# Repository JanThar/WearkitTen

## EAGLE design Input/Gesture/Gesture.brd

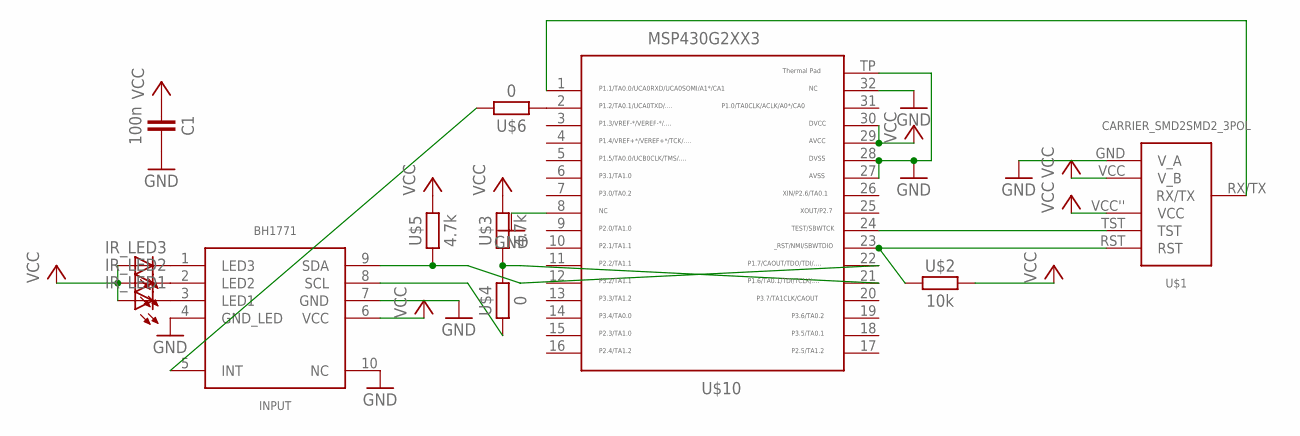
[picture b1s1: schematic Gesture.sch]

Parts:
C1: 100n; 603
INPUT: BH1771
IR_LED1, IR_LED2, IR_LED3: LEDCHIP-LED0603; CHIP-LED0603
U$1: CARRIER_SMD2SMD2_3POL; CARRIER_SMD2_3POL
U$2: 10k; 603
U$3, U$5: 4.7k; 603
U$4, U$6: 0; 603
U$10: MSP430G2553; QFN32

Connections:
GND: C1.2, INPUT.4 (GND_LED), INPUT.7 (GND), INPUT.10 (NC), U$1.GND (V_A), U$10.8, U$10.27, U$10.28, U$10.32, U$10.TP
unnamed: U$6.1, U$10.2
unnamed: U$1.TST, U$10.24
unnamed: U$1.RST, U$2.1, U$10.23
unnamed: U$3.1, U$4.2, U$10.21
unnamed: INPUT.5 (INT), U$6.2
unnamed: U$1.RX/TX, U$10.1
unnamed: INPUT.9 (SDA), U$5.1, U$10.22
unnamed: INPUT.8 (SCL), U$4.1
unnamed: INPUT.1 (LED3), IR_LED3.C
unnamed: INPUT.2 (LED2), IR_LED2.C
unnamed: INPUT.3 (LED1), IR_LED1.C
VCC: C1.1, INPUT.6 (VCC), IR_LED1.A, IR_LED2.A, IR_LED3.A, U$1.VCC (V_B), U$1.VCC'' (VCC), U$2.2, U$3.2, U$5.2, U$10.29, U$10.30

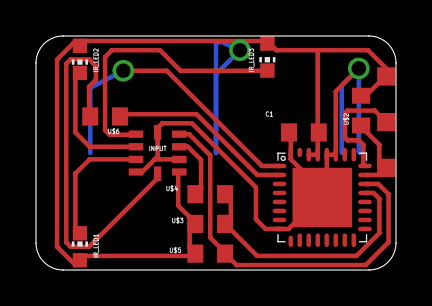
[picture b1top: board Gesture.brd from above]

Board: 2 copper layers, 20.0 x 13.0 mm, 12 parts (0 on the bottom side), 13 nets.

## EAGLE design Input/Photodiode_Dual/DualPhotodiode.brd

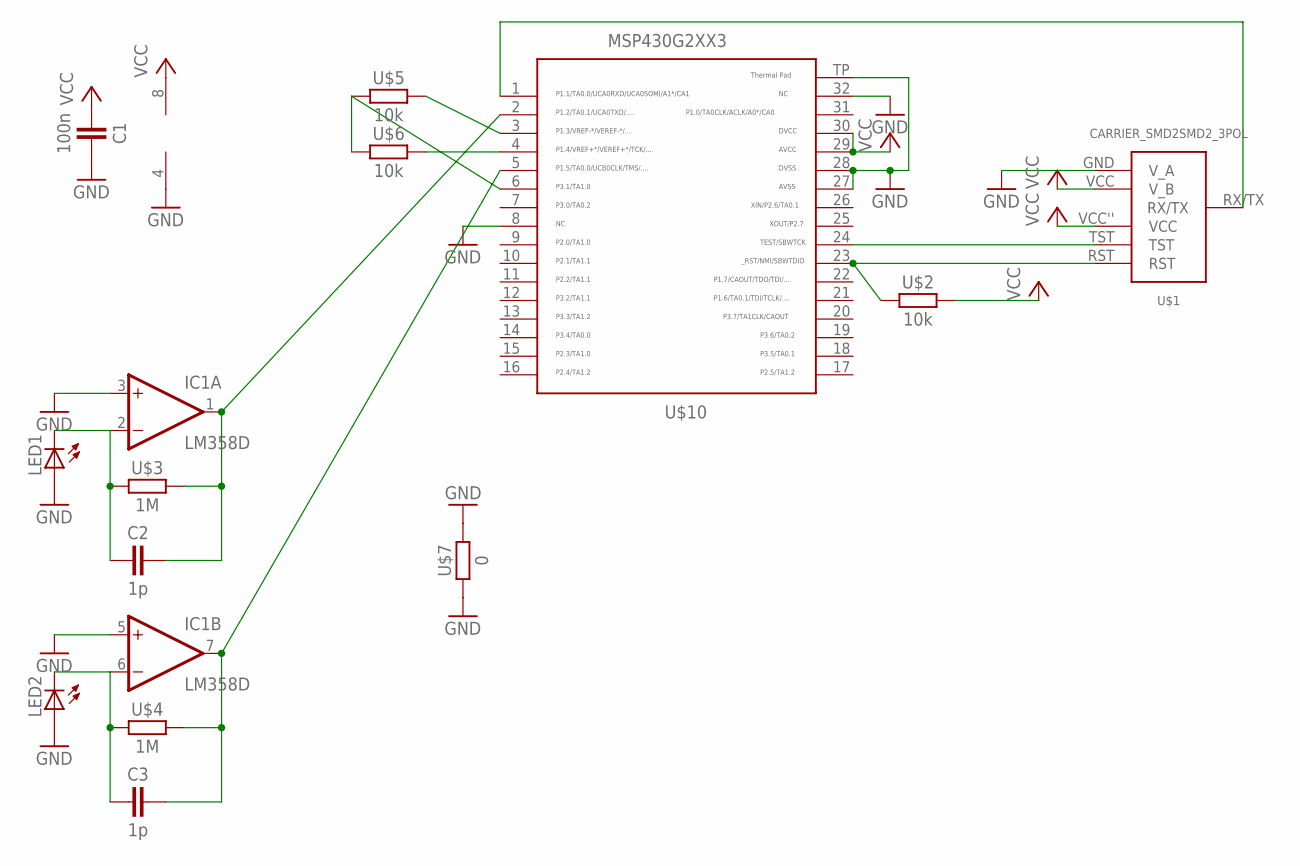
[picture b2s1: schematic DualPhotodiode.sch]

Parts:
C1: 100n; 603
C2, C3: 1p; 603
IC1: LM358D; SO08
LED1, LED2: LEDCHIP-LED0805; CHIP-LED0805
U$1: CARRIER_SMD2SMD2_3POL; CARRIER_SMD2_3POL
U$2, U$5, U$6: 10k; 603
U$3, U$4: 1M; 603
U$7: 0; 603
U$10: MSP430G2553; QFN32

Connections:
GND: C1.2, IC1.3 (+IN), IC1.4 (V-), IC1.5 (+IN), LED1.A, LED2.A, U$1.GND (V_A), U$7.1, U$7.2, U$10.8, U$10.27, U$10.28, U$10.32, U$10.TP
unnamed: C2.1, IC1.2 (-IN), LED1.C, U$3.1
unnamed: U$1.TST, U$10.24
unnamed: U$1.RST, U$2.1, U$10.23
unnamed: U$5.2, U$10.3
unnamed: C3.1, IC1.6 (-IN), LED2.C, U$4.1
unnamed: C3.2, IC1.7 (OUT), U$4.2, U$10.5
unnamed: C2.2, IC1.1 (OUT), U$3.2, U$10.2
unnamed: U$1.RX/TX, U$10.1
unnamed: U$6.2, U$10.4
unnamed: U$5.1, U$6.1, U$10.6
VCC: C1.1, IC1.8 (V+), U$1.VCC (V_B), U$1.VCC'' (VCC), U$2.2, U$10.29, U$10.30

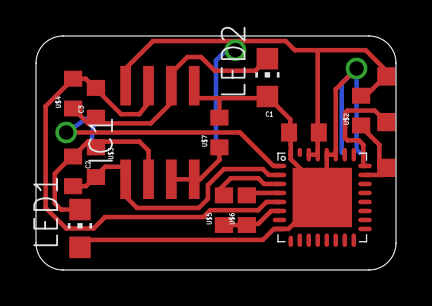
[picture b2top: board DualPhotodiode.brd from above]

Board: 2 copper layers, 20.0 x 13.0 mm, 14 parts (0 on the bottom side), 12 nets.

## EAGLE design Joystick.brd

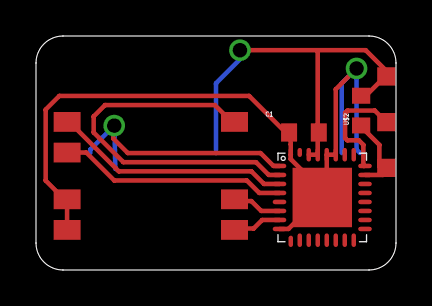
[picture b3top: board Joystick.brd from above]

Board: 2 copper layers, 20.0 x 13.0 mm, 5 parts (0 on the bottom side), 10 nets.

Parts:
C1: 100n; 603
U$1: CARRIER_SMD2SMD2_3POL; CARRIER_SMD2_3POL
U$2: 10k; 603
U$3: JOYSTICK
U$10: MSP430G2553; QFN32

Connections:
D: U$3.D4, U$10.7
GND: C1.2, U$1.GND, U$3.C1, U$3.C2, U$10.8, U$10.27, U$10.28, U$10.32, U$10.TP
L: U$3.L7, U$10.3
unnamed: U$1.TST, U$10.24
unnamed: U$1.RST, U$2.1, U$10.23
unnamed: U$1.RX/TX, U$10.1
R: U$3.R6, U$10.4
SELECT: U$3.S5, U$10.2
U: U$3.U3, U$10.6
VCC: C1.1, U$1.VCC, U$1.VCC'', U$2.2, U$10.29, U$10.30

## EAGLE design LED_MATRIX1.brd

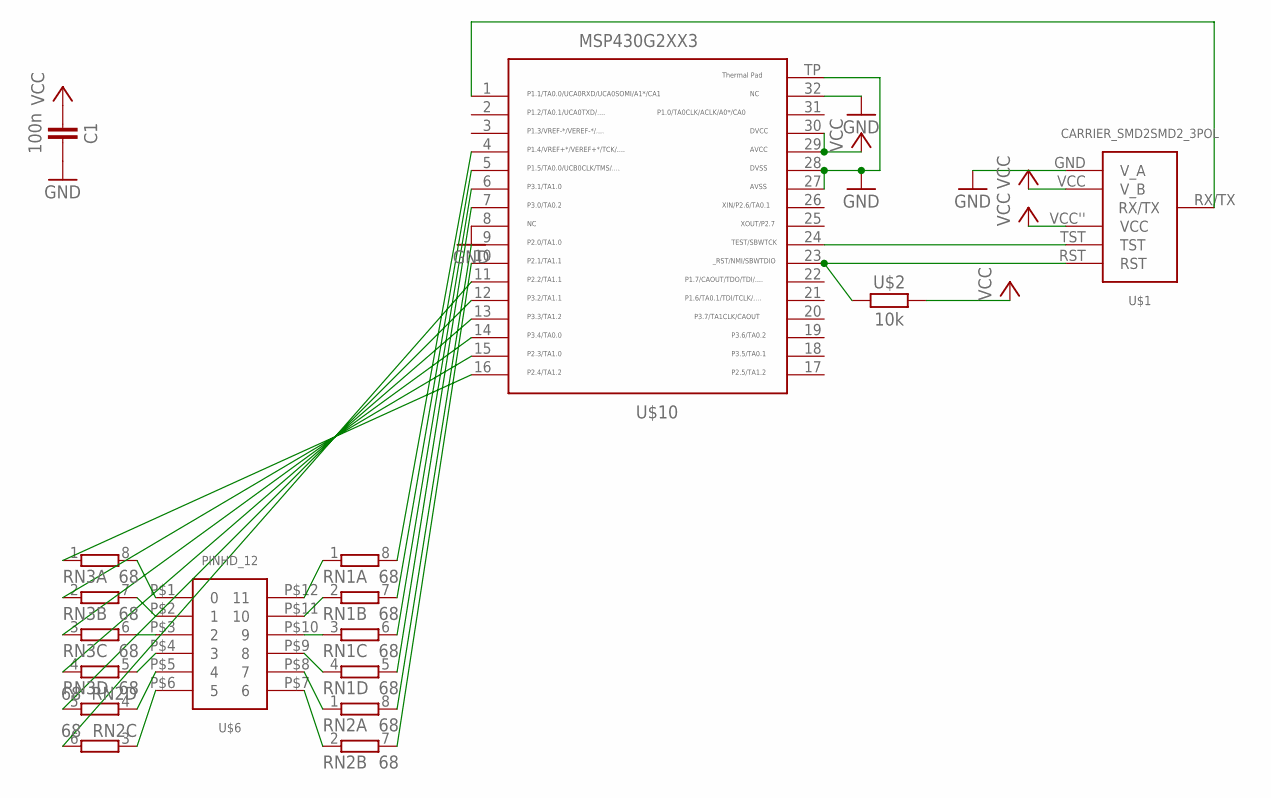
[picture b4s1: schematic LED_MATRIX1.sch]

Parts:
C1: 100n; 603
RN1, RN2, RN3: 68; 0603-ARC
U$1: CARRIER_SMD2SMD2_3POL; CARRIER_SMD2_3POL
U$2: 10k; 603
U$6: PINHD_12; FFC12/1MM
U$10: MSP430G2553; QFN32

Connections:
GND: C1.2, U$1.GND (V_A), U$10.8, U$10.27, U$10.28, U$10.32, U$10.TP
unnamed: RN3.1, U$10.16
unnamed: U$1.TST, U$10.24
unnamed: U$1.RST, U$2.1, U$10.23
unnamed: RN3.7 (2), U$6.P$2 (1)
unnamed: RN3.2 (1), U$10.15
unnamed: RN3.3 (1), U$10.14
unnamed: RN3.4 (1), U$10.13
unnamed: U$1.RX/TX, U$10.1
unnamed: RN2.5 (2), U$10.12
unnamed: RN2.6 (2), U$10.11
unnamed: RN2.7 (2), U$10.10
unnamed: RN2.8 (2), U$10.9
unnamed: RN1.5 (2), U$10.7
unnamed: RN1.6 (2), U$10.6
unnamed: RN1.7 (2), U$10.5
unnamed: RN1.8 (2), U$10.4
unnamed: RN1.1, U$6.P$12 (11)
unnamed: RN1.2 (1), U$6.P$11 (10)
unnamed: RN1.3 (1), U$6.P$10 (9)
unnamed: RN1.4 (1), U$6.P$9 (8)
unnamed: RN2.1, U$6.P$8 (7)
unnamed: RN2.2 (1), U$6.P$7 (6)
unnamed: RN2.3 (1), U$6.P$6 (5)
unnamed: RN2.4 (1), U$6.P$5 (4)
unnamed: RN3.5 (2), U$6.P$4 (3)
unnamed: RN3.6 (2), U$6.P$3 (2)
unnamed: RN3.8 (2), U$6.P$1 (0)
VCC: C1.1, U$1.VCC (V_B), U$1.VCC'' (VCC), U$2.2, U$10.29, U$10.30

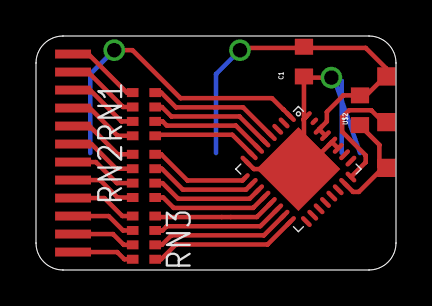
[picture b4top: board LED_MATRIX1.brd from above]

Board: 2 copper layers, 20.0 x 13.0 mm, 8 parts (0 on the bottom side), 29 nets.

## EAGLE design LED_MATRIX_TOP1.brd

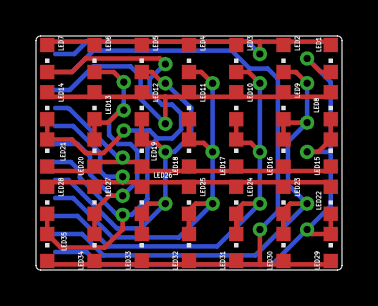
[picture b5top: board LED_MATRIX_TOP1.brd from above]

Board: 2 copper layers, 17.0 x 13.0 mm, 36 parts (1 on the bottom side), 12 nets.

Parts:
LED1, LED2, LED3, LED4, LED5, LED6, LED7, LED8, LED9, LED10, LED11, LED12, LED13, LED14, LED15, LED16, LED17, LED18, LED19, LED20, LED21, LED22, LED23, LED24, LED25, LED26, LED27, LED28, LED29, LED30, LED31, LED32, LED33, LED34, LED35: CHIPLED_0603
U$1: PINHD_12; FFC12/1MM

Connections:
unnamed: LED1.A, LED2.A, LED3.A, LED4.A, LED5.A, LED6.A, LED7.A, U$1.P$1
unnamed: LED8.A, LED9.A, LED10.A, LED11.A, LED12.A, LED13.A, LED14.A, U$1.P$3
unnamed: LED15.A, LED16.A, LED17.A, LED18.A, LED19.A, LED20.A, LED21.A, U$1.P$4
unnamed: LED22.A, LED23.A, LED24.A, LED25.A, LED26.A, LED27.A, LED28.A, U$1.P$5
unnamed: LED29.A, LED30.A, LED31.A, LED32.A, LED33.A, LED34.A, LED35.A, U$1.P$2
unnamed: LED1.C, LED8.C, LED15.C, LED22.C, LED29.C, U$1.P$12
unnamed: LED2.C, LED9.C, LED16.C, LED23.C, LED30.C, U$1.P$11
unnamed: LED3.C, LED10.C, LED17.C, LED24.C, LED31.C, U$1.P$10
unnamed: LED4.C, LED11.C, LED18.C, LED25.C, LED32.C, U$1.P$9
unnamed: LED5.C, LED12.C, LED19.C, LED26.C, LED33.C, U$1.P$8
unnamed: LED6.C, LED13.C, LED20.C, LED27.C, LED34.C, U$1.P$6
unnamed: LED7.C, LED14.C, LED21.C, LED28.C, LED35.C, U$1.P$7

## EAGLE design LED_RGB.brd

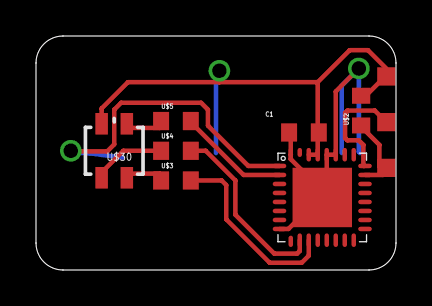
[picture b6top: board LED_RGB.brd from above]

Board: 2 copper layers, 20.0 x 13.0 mm, 8 parts (0 on the bottom side), 11 nets.

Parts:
C1: 100n; 603
U$1: CARRIER_SMD2SMD2_3POL; CARRIER_SMD2_3POL
U$2: 10k; 603
U$3, U$4, U$5: 150; 603
U$10: MSP430G2553; QFN32
U$30: LED-TRICOLOR; LED-TRICOLOR-SMD

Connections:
GND: C1.2, U$1.GND, U$10.8, U$10.27, U$10.28, U$10.32, U$10.TP
unnamed: U$3.1, U$30.G
unnamed: U$1.TST, U$10.24
unnamed: U$1.RST, U$2.1, U$10.23
unnamed: U$4.1, U$30.B
unnamed: U$5.1, U$30.R
unnamed: U$4.2, U$10.10
unnamed: U$5.2, U$10.2
unnamed: U$1.RX/TX, U$10.1
unnamed: U$3.2, U$10.11
VCC: C1.1, U$1.VCC, U$1.VCC'', U$2.2, U$10.29, U$10.30, U$30.A

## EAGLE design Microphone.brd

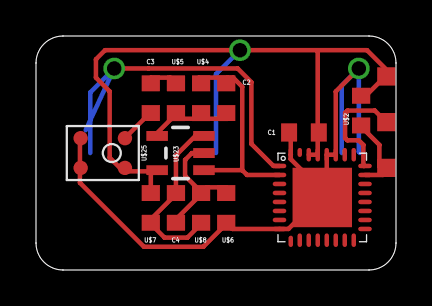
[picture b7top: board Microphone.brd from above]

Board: 2 copper layers, 20.0 x 13.0 mm, 14 parts (0 on the bottom side), 11 nets.

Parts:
C1: 100n; 603
C2: 100p; 603
C3, C4: 1µ; 603
U$1: CARRIER_SMD2SMD2_3POL; CARRIER_SMD2_3POL
U$2, U$7, U$8: 10k; 603
U$4: 100k; 603
U$5: 1.5k; 603
U$6: 2k; 603
U$10: MSP430G2553; QFN32
U$23: OPA344; SOT23-5
U$25: WM7120A

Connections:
GND: C1.2, U$1.GND, U$6.2, U$10.8, U$10.27, U$10.28, U$10.32, U$10.TP, U$25.2, U$25.3
unnamed: C3.1, U$25.4
unnamed: U$1.TST, U$10.24
unnamed: U$1.RST, U$2.1, U$10.23
unnamed: U$1.RX/TX, U$10.1
unnamed: C2.1, U$4.1, U$5.2, U$23.4
unnamed: C3.2, U$5.1
unnamed: C4.1, U$6.1, U$8.1, U$23.2
unnamed: C4.2, U$7.2, U$8.2, U$23.3
SOUND: C2.2, U$4.2, U$10.2, U$23.1
VCC: C1.1, U$1.VCC, U$1.VCC'', U$2.2, U$7.1, U$10.29, U$10.30, U$23.5, U$25.1

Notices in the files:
parts and their libraries:
SparkFun-LED: Licensing: CC v3.0 Share-Alike You are welcome to use this library for commercial purposes.
